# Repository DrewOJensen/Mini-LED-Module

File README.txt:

Mini LED Module

This project started out as my first schematic to prototype project. It's a very simple LED module that has a small through hole switch, 0603 resistor, 5mm LED and a CR2032 battery. The LED is placed on the back side since the original project required it. This board was create to hang in the top of a rice lantern and illuminate from the bottom side. Can be used in many other applications.

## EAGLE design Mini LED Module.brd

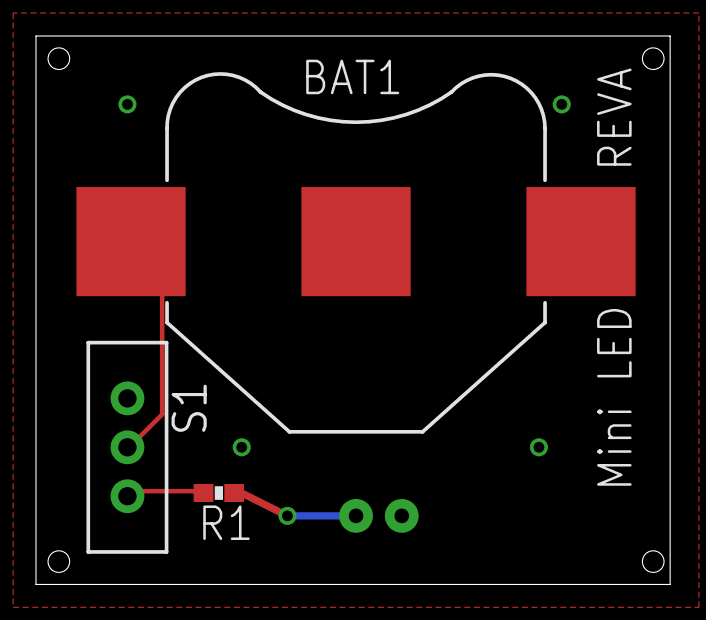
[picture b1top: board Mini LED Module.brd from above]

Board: 2 copper layers, 35.2 x 30.5 mm, 4 parts (1 on the bottom side), 3 nets.

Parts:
BAT1: 3V; BATTCON_20MM
LED: ORNG; LED5MM-KIT
R1: 51Ω; 0603-RES
S1: SWITCH-SPDT_KIT

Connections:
GND: BAT1.2, LED.K
unnamed: R1.1, S1.1
unnamed: BAT1.1, S1.2

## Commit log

2013-03-21 Initial Upload

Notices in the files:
parts and their libraries:
SparkFun-LED: Licensing: CC v3.0 Share-Alike You are welcome to use this library for commercial purposes.
